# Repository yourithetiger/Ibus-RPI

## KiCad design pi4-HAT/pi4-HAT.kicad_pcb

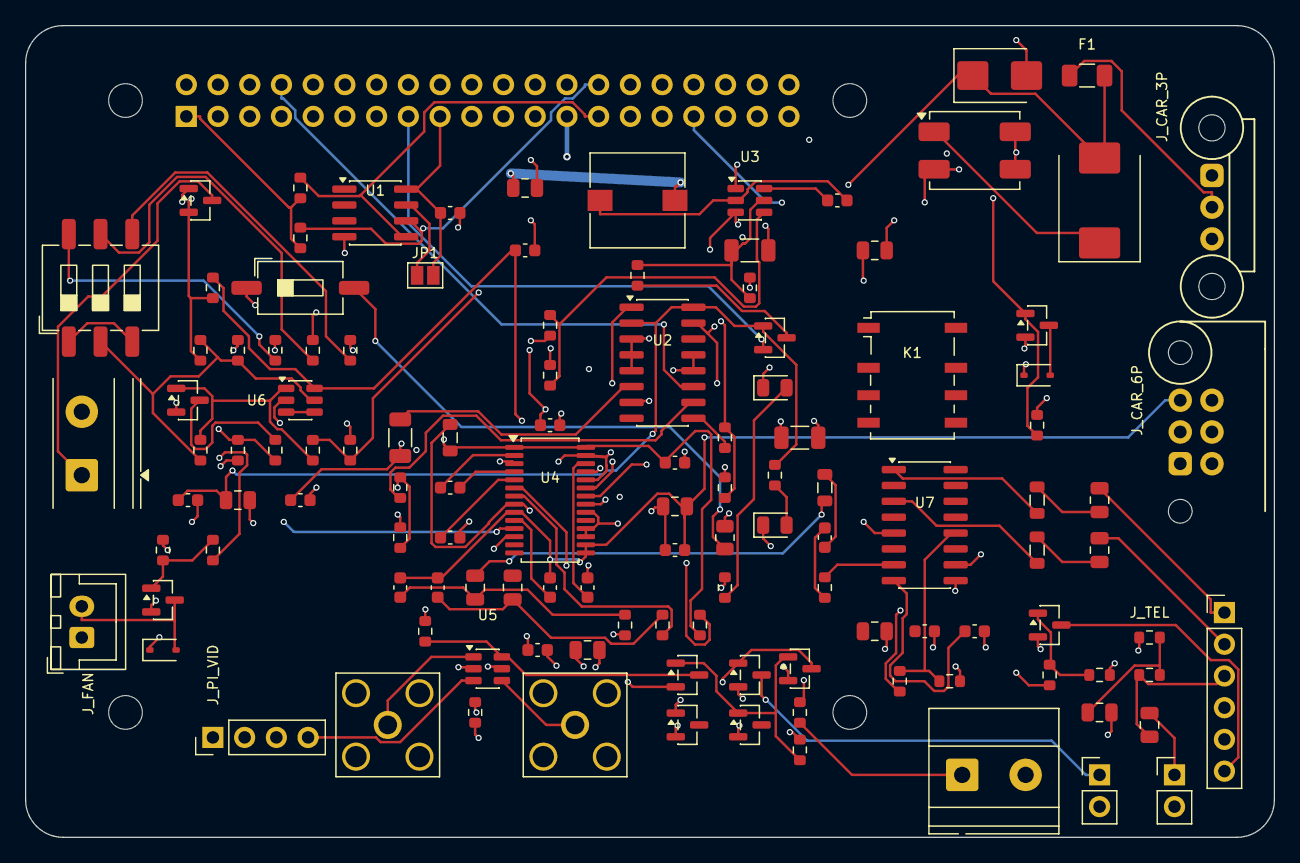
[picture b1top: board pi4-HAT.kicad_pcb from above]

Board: 4 copper layers, 100.0 x 65.0 mm, 125 parts (1 on the bottom side), 91 nets.

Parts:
C1: 100n; C_0603_1608Metric
C2: 10uF_50V; C_1206_3216Metric
C3, C5, C11, C14, C16, C22, C23, C25: 100nF; C_0603_1608Metric
C4: 47uF; C_1206_3216Metric
C6, C7: 22uF; C_0805_2012Metric
C9: 220pF; C_0603_1608Metric
C10, C15, C19, C20, C24, C26, C30, C31, C32, C33: 10uF; C_0805_2012Metric
C12, C13: 2.2uF; C_0603_1608Metric
C17, C18: 2.2nF; C_0603_1608Metric
C21: 10uF; C_0603_1608Metric
C27: 0.1uF; C_0603_1608Metric
C28, C29: 1uF; C_0603_1608Metric
D1: SMBJ18A; D_SMB
D2: SS34; D_SMC
D3, D9, D11: BAT54C; SOT-23
D4: GREEN; LED_0805_2012Metric
D5: BLUE; LED_0805_2012Metric
D7, D10: 1N4148; D_SOD-323
D8: BZX84C3V3; SOT-23
D12: BZX84C4V7; SOT-23
F1: 5A; Fuse_1206_3216Metric
FB1, FB2, FB3: 120R/2A; L_0805_2012Metric
FL1: ACM70V-701-2PL; L_CommonModeChoke_TDK_ACM7060
J1: GPIO; PinSocket_2x20_P2.54mm_Vertical
JP1: ID_WP; SolderJumper-2_P1.3mm_Open_Pad1.0x1.5mm
J_CAR_3P: TE_953442-1; TE_MQS_3PIN
J_CAR_6P: TE_966871-1; TE_MQS_6PIN
J_DVR: TE_MKDS_2P; TerminalBlock_Phoenix_MKDS-1,5-2-5.08_1x02_P5.08mm_Horizont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
J_FAN: JST_2P_FAN; JST_XH_B2B-XH-A_1x02_P2.50mm_Vertical
J_MIC: MIC_OUT_USB; PinHeader_1x02_P2.54mm_Vertical
J_PI_VID: TRRS_3.5mm_PI; PinHeader_1x04_P2.54mm_Vertical
J_RCA_CAM: RCA_CAM_IN; SMA_Amphenol_132203-12_Horizontal
J_RCA_TV: RCA_TV_OUT; SMA_Amphenol_132203-12_Horizontal
J_REV: MKDS_REV_12V; TerminalBlock_Phoenix_MKDS-1,5-2-5.08_1x02_P5.08mm_Horizont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
J_TEL: TCU_IO_DB25; PinHeader_1x06_P2.54mm_Vertical
J_TV_TRIG: TV_PIN17_TRIG; PinHeader_1x02_P2.54mm_Vertical
K1: G6K-2F-Y-5VDC; Relay_DPDT_Omron_G6K-2F-Y
L1: 10uH; L_Wuerth_WE-PD-Typ-7345
L2: BLM21PG221SN1D; L_0805_2012Metric
MH1, MH2, MH3, MH4: MountingHole_2.7mm_M2.5
Q1, Q2, Q3, Q5, Q6: 2N7002; SOT-23
Q4: DMP32D4S; SOT-23
R1, R2: 3.9k; R_0603_1608Metric
R3: 100k_1%; R_0603_1608Metric
R4: 13.3k_1%; R_0603_1608Metric
R5, R8, R10, R13, R14, R39, R41: 1k; R_0603_1608Metric
R6: 1M; R_0603_1608Metric
R7: 10_1W; R_1206_3216Metric
R9, R11: 2k; R_0603_1608Metric
R12: 10k; R_0805_2012Metric
R16, R24, R25, R26, R35, R36, R40, R42: 100k; R_0603_1608Metric
R17, R18: 470; R_0603_1608Metric
R19, R22, R37, R43: 10k; R_0603_1608Metric
R23: 3.3k; R_0603_1608Metric
R27, R44: 100; R_0603_1608Metric
R28: 680k; R_0603_1608Metric
R29: 1.00M_1%; R_0603_1608Metric
R30: 1.00M; R_0603_1608Metric
R31: 118k_1%; R_0603_1608Metric
R32: 115k_1%; R_0603_1608Metric
R33: 113k_1%; R_0603_1608Metric
R34: 10M; R_0603_1608Metric
R38: 20k; R_0603_1608Metric
R45: 2.2k; R_0603_1608Metric
SW_BENCH: SW_BENCH; SW_DIP_SPSTx01_Slide_6.7x4.1mm_W8.61mm_P2.54mm_LowProfile
SW_DVR_CFG: DIP-3; SW_DIP_SPSTx03_Slide_6.7x9.18mm_W8.61mm_P2.54mm_LowProfile
U1: CAT24C256; SOIC-8_3.9x4.9mm_P1.27mm
U2: TH3122.4; SOIC-16_3.9x9.9mm_P1.27mm
U3: TPS54302; SOT-23-6
U4: PCM5122PW; TSSOP-28_4.4x9.7mm_P0.65mm
U5: TS5A3159; SOT-23-6
U6: TLV3012; SOT-23-6
U7: PAM8406D; SOIC-16_3.9x9.9mm_P1.27mm

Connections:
+3V3: C1.1, C14.1, J1.1, J1.17, JP1.2, L2.1, R1.1, R2.1, R19.1, U1.8, U4.1, U4.28
+5V: C6.1, C7.1, C23.1, C24.1, D7.1, D10.1, J1.2, J1.4, J_FAN.1, L1.2, R3.1, R13.2, R44.1, U5.5, U7.5, U7.9
+12V_IN: C2.1, C3.1, FL1.2, SW_BENCH.1, U2.1, U2.15, U3.3
AGND: C15.2, C16.2, C17.2, C18.2, C21.2, J_CAR_6P.3, J_CAR_6P.6, U4.9, U4.15, U4.16
AVDD_3V3: C15.1, C16.1, L2.2, U4.8
BENCH_PULLUP: R12.1, SW_BENCH.2
BOOT_NODE: C5.1, U3.6
BUCK_EN: C4.1, R5.2, R6.1, U3.5
BUCK_FB: R3.2, R4.1, U3.4
CAM_TRIG_GND: J_TV_TRIG.1, Q2.3
CAM_VID: J_RCA_CAM.1, U5.1
DAC_CAPM: C12.2, U4.4
DAC_CAPP: C12.1, U4.2
DAC_FLT_L: C17.1, C19.1, R17.2
DAC_FLT_R: C18.1, C20.1, R18.2
DAC_LDOO: C22.1, U4.26
DAC_OUTL_RAW: R17.1, U4.6
DAC_OUTR_RAW: R18.1, U4.7
DAC_VCOM: C21.1, U4.10
DAC_VNEG: C13.1, U4.5
DAC_XSMT: R19.2, U4.25
DVR_12V_OUT: J_DVR.1, Q4.3
DVR_COMP_OUT: Q3.1, R34.2, R37.1, U6.1
DVR_GATE_PULL: Q3.3, R36.2
DVR_PMOS_GATE: Q4.1, R35.2, R36.1
DVR_SENSE: R29.2, R30.1, R34.1, SW_DVR_CFG.2, U6.5
DVR_VCC_5V: C25.1, D12.1, R28.2, U6.6
FAN_GATE: Q5.1, R26.1, R27.2
FAN_NEG: D10.2, J_FAN.2, Q5.3
GND: C1.2, C2.2, C3.2, C4.2, C6.2, C7.2, C9.2, C10.2, C11.2, C13.2, C14.2, C22.2, C23.2, C24.2, C25.2, C26.2, C27.2, C28.2, C32.2, D1.2, D4.1, D5.1, D8.2, D12.2, FL1.3, FL1.4, J1.6, J1.9, J1.14, J1.20, J1.25, J1.30, J1.34, J1.39, J_CAR_3P.1, J_DVR.2, J_MIC.2, J_PI_VID.3, J_RCA_CAM.2, J_RCA_TV.2, J_REV.2, J_TEL.4, J_TV_TRIG.2, Q1.2, Q2.2, Q3.2, Q5.2, Q6.2, R4.2, R6.2, R9.2, R11.2, R16.2, R23.2, R24.2, R25.2, R26.2, R30.2, R31.2, R32.2, R33.2, R38.2, R40.2, R42.2, U1.4, U2.3, U2.4, U2.5, U2.7, U2.12, U2.13, U3.1, U4.3, U4.17, U4.18, U4.20, U4.24, U4.27, U5.2, U6.2, U7.10
GPIO2/SDA1: J1.3, U4.11
GPIO3/SCL1: J1.5, U4.12
GPIO12/PWM0: J1.32, R27.1
GPIO13/PWM1: J1.33, R22.2
GPIO14/TXD0: J1.8, U2.11
GPIO15/RXD0: J1.10, R8.2, R9.1
GPIO16: J1.36, R10.2, R11.1
GPIO17: J1.11, R41.1
GPIO18/PCM.CLK: J1.12, U4.21
GPIO19/PCM.FS: J1.35, U4.23
GPIO21/PCM.DOUT: J1.40, U4.22
GPIO22: D3.2, J1.15
GPIO23: J1.16, R39.1
GPIO24: D11.2, J1.18
GPIO25: D9.2, J1.22
GPIO26: J1.37, R37.2, R38.1
IBUS: C9.1, J_CAR_3P.3, R7.1, R12.2
IBUS_5V: C10.1, C11.1, D3.1, R14.2, U2.2, U2.16
ID_SCL: J1.28, R2.2, U1.6
ID_SDA: J1.27, R1.2, U1.5
KL30: F1.1, J_CAR_3P.2
LED_5V_ANODE: D4.2, R13.1
LED_IBUS_ANODE: D5.2, R14.1
unnamed: C28.1, U7.8
unnamed: C29.1, FB3.2
unnamed: C29.2, R43.1
unnamed: C30.1, FB1.2
unnamed: C30.2, J_TEL.1
unnamed: C31.1, FB2.2
unnamed: C31.2, J_TEL.2
unnamed: C32.1, R44.2, R45.2
unnamed: C33.1, J_TEL.3, R45.1
unnamed: C33.2, J_MIC.1
unnamed: FB1.1, U7.1
unnamed: FB2.1, U7.3
unnamed: JP1.1, U1.7
unnamed: J_TEL.6, Q6.3
unnamed: Q6.1, R39.2, R40.1
unnamed: R31.1, SW_DVR_CFG.6
unnamed: R32.1, SW_DVR_CFG.5
unnamed: R33.1, SW_DVR_CFG.4
unnamed: R41.2, R42.1, U7.12
unnamed: R43.2, U7.7
unnamed: SW_DVR_CFG.1, SW_DVR_CFG.3
unnamed: U6.3, U6.4
PI_AUDIO_L: C19.2, FB3.1
PI_VID: J_PI_VID.4, U5.3
PWR_KEEP_ALIVE: D3.3, R5.1
RELAY_COIL_NEG: D7.2, Q1.3
RELAY_CTRL: J1.13, Q1.1, R16.1
REV_12V_IN: J_REV.1, R22.1
REV_SENSE_3V3: D8.1, D9.1, D11.1, R23.1
SW_NODE: C5.2, L1.1, U3.2
TH3122_IBUS: R7.2, U2.6
TH3122_RXD: R8.1, U2.10
TH3122_SEN_STA: R10.1, U2.9
TV_TRIG_GATE: D9.3, Q2.1, R25.1
TV_VID_OUT: J_RCA_TV.1, U5.4
VFILT: D2.1, FL1.1
VID_SEL: D11.3, R24.1, U5.6
VRAW: D1.1, D2.2, F1.2, Q4.2, R28.1, R29.1, R35.1

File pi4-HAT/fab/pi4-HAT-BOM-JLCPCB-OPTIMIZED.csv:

Comment,Designator,Footprint,LCSC Part #
100nF,"C1,C3,C5,C11,C14,C16,C22,C23,C25,C27",C_0603_1608Metric,C14663
10uF,C2,C_1206_3216Metric,C13585
47uF,C4,C_1206_3216Metric,C96937
22uF,"C6,C7",C_0805_2012Metric,C45783
220pF,C9,C_0603_1608Metric,C1600
10uF,"C10,C15,C19,C20,C24,C26,C30,C31,C32,C33",C_0805_2012Metric,C15850
2.2uF,"C12,C13",C_0603_1608Metric,C23630
2.2nF,"C17,C18",C_0603_1608Metric,C1591
10uF,C21,C_0603_1608Metric,C19702
1uF,"C28,C29",C_0603_1608Metric,C15849
BAT54C,"D3,D9,D11",SOT-23,C8596
GREEN,D4,LED_0805_2012Metric,C2297
BLUE,D5,LED_0805_2012Metric,C2293
1N4148,"D7,D10",D_SOD-323,C81598
BZX84C3V3,D8,SOT-23,C8675
120R/2A,"FB1,FB2,FB3",L_0805_2012Metric,C1015
BLM21PG221SN1D,L2,L_0805_2012Metric,C1035
2N7002,"Q1,Q2,Q3,Q5,Q6",SOT-23,C8598
DMP32D4S,Q4,SOT-23,C151273
3.9k,"R1,R2",R_0603_1608Metric,C22985
100k,"R3,R16,R24,R25,R26,R35,R36,R40,R42",R_0603_1608Metric,C25803
1k,"R5,R8,R10,R13,R14,R39,R41",R_0603_1608Metric,C21190
1M,"R6,R29,R30",R_0603_1608Metric,C22935
10,R7,R_1206_3216Metric,C17935
2k,"R9,R11",R_0603_1608Metric,C21198
10k,R12,R_0805_2012Metric,C17414
470,"R17,R18",R_0603_1608Metric,C23179
10k,"R19,R22,R37,R43",R_0603_1608Metric,C25804
3.3k,R23,R_0603_1608Metric,C22978
100,"R27,R44",R_0603_1608Metric,C22775
680k,R28,R_0603_1608Metric,C23206
10M,R34,R_0603_1608Metric,C125141
20k,R38,R_0603_1608Metric,C25760
2.2k,R45,R_0603_1608Metric,C21199
CAT24C256,U1,SOIC-8_3.9x4.9mm_P1.27mm,C146734
TPS54302,U3,SOT-23-6,C311983
PCM5122PW,U4,TSSOP-28_4.4x9.7mm_P0.65mm,C962071
TS5A3159,U5,SOT-23-6,C92485
PAM8406D,U7,SOIC-16_3.9x9.9mm_P1.27mm,C86270

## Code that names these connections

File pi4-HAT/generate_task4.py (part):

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import uuid
import shutil

SCHEMATIC_PATH = "/home/Youri621/E39Project/Ibus-RPI/pi4-HAT/pi4-HAT.kicad_sch"
BACKUP_PATH = "/home/Youri621/E39Project/Ibus-RPI/pi4-HAT/pi4-HAT.kicad_sch.bak_task3"

# Restore clean backup from task 3
shutil.copy(BACKUP_PATH, SCHEMATIC_PATH)
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# BLOCK A: Autonomous Low-Voltage Cutoff for DVR (X: 320..415, Y: 85..155)
# =========================================================================
# R28 (680k) rot=90: local pins (0, 2.54), (0, -2.54)
# pin 1: transform(325.12, 91.44, 0, 2.54, 90) = (322.58, 91.44) -> VRAW
# pin 2: transform(325.12, 91.44, 0, -2.54, 90) = (327.66, 91.44) -> DVR_VCC_5V
add_inst("Device:R_Small", "R28", "680k", "Resistor_SMD:R_0603_1608Metric", 325.12, 91.44, rot=90, pin_count=2)
p1 = transform(325.12, 91.44, 0, 2.54, 90)
p2 = transform(325.12, 91.44, 0, -2.54, 90)
add_label("VRAW", p1[0], p1[1], rot=180)
add_label("DVR_VCC_5V", p2[0], p2[1], rot=0)

# D12 (BZX84C4V7 Zener) rot=90: local pins K: (-2.54, 0), A: (2.54, 0)
# K: transform(335.28, 91.44, -2.54, 0, 90) = (335.28, 93.98) -> DVR_VCC_5V
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add_inst("Device:D_Zener_Small", "D12", "BZX84C4V7", "Package_TO_SOT_SMD:SOT-23", 335.28, 91.44, rot=90, pin_count=2)
pk = transform(335.28, 91.44, -2.54, 0, 90)
pa = transform(335.28, 91.44, 2.54, 0, 90)
add_label("DVR_VCC_5V", pk[0], pk[1], rot=270)
add_label("GND", pa[0], pa[1], rot=90)

# C25 (100nF) rot=0: local pins (0, 2.54), (0, -2.54)
# pin 1: (345.44, 91.44 - 2.54) = (345.44, 88.9) -> DVR_VCC_5V
# pin 2: (345.44, 91.44 + 2.54) = (345.44, 93.98) -> GND
add_inst("Device:C_Small", "C25", "100nF", "Capacitor_SMD:C_0603_1608Metric", 345.44, 91.44, rot=0, pin_count=2)
p1 = transform(345.44, 91.44, 0, 2.54, 0)
p2 = transform(345.44, 91.44, 0, -2.54, 0)
add_label("DVR_VCC_5V", p1[0], p1[1], rot=90)
add_label("GND", p2[0], p2[1], rot=270)
# Add PWR_FLAG on DVR_VCC_5V
add_pwr_flag(p1[0], p1[1])
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p_inp = transform(355.6, 121.92, -10.16, 3.81, 0)
p_vcc = transform(355.6, 121.92, 0, 8.89, 0)

add_label("DVR_COMP_OUT", p_out[0], p_out[1], rot=0)
add_label("GND", p_gnd[0], p_gnd[1], rot=270)
add_label("DVR_SENSE", p_inp[0], p_inp[1], rot=180)
add_label("DVR_VCC_5V", p_vcc[0], p_vcc[1], rot=90)
# Connect Pin 3 (REF) to Pin 4 (IN-)
add_wire(p_ref[0], p_ref[1], p_ref[0] - 2.54, p_ref[1])
add_wire(p_ref[0] - 2.54, p_ref[1], p_inm[0] - 2.54, p_inm[1])
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add_inst("Device:R_Small", "R29", "1.00M_1%", "Resistor_SMD:R_0603_1608Metric", 325.12, 114.3, rot=90, pin_count=2)
p1 = transform(325.12, 114.3, 0, 2.54, 90)
p2 = transform(325.12, 114.3, 0, -2.54, 90)
add_label("VRAW", p1[0], p1[1], rot=180)
add_label("DVR_SENSE", p2[0], p2[1], rot=0)

add_inst("Device:R_Small", "R30", "1.00M", "Resistor_SMD:R_0603_1608Metric", 325.12, 127.0, rot=90, pin_count=2)
p1 = transform(325.12, 127.0, 0, 2.54, 90)
p2 = transform(325.12, 127.0, 0, -2.54, 90)
add_label("DVR_SENSE", p1[0], p1[1], rot=180)
add_label("GND", p2[0], p2[1], rot=0)

add_inst("Device:R_Small", "R34", "10M", "Resistor_SMD:R_0603_1608Metric", 355.6, 142.24, rot=90, pin_count=2)
p1 = transform(355.6, 142.24, 0, 2.54, 90)
p2 = transform(355.6, 142.24, 0, -2.54, 90)
add_label("DVR_SENSE", p1[0], p1[1], rot=180)
add_label("DVR_COMP_OUT", p2[0], p2[1], rot=0)

# DIP Switch SW_DVR_CFG at (325.12, 149.86) rot=0
# Left pins:
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p_sw2 = transform(325.12, 149.86, -7.62, 0, 0)
p_sw3 = transform(325.12, 149.86, -7.62, -2.54, 0)
add_wire(p_sw1[0], p_sw1[1], p_sw3[0], p_sw3[1])
add_label("DVR_SENSE", p_sw2[0], p_sw2[1], rot=180)

p_sw6 = transform(325.12, 149.86, 7.62, 2.54, 0)
p_sw5 = transform(325.12, 149.86, 7.62, 0, 0)
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q3_g = transform(381.0, 121.92, -5.08, 0, 0)
q3_s = transform(381.0, 121.92, 2.54, -5.08, 0)
q3_d = transform(381.0, 121.92, 2.54, 5.08, 0)
add_label("DVR_COMP_OUT", q3_g[0], q3_g[1], rot=180)
add_label("GND", q3_s[0], q3_s[1], rot=270)
add_label("DVR_GATE_PULL", q3_d[0], q3_d[1], rot=90)

# R35 (100k) & R36 (100k)
add_inst("Device:R_Small", "R35", "100k", "Resistor_SMD:R_0603_1608Metric", 393.7, 104.14, rot=90, pin_count=2)
p1 = transform(393.7, 104.14, 0, 2.54, 90)
p2 = transform(393.7, 104.14, 0, -2.54, 90)
add_label("VRAW", p1[0], p1[1], rot=180)
add_label("DVR_PMOS_GATE", p2[0], p2[1], rot=0)

add_inst("Device:R_Small", "R36", "100k", "Resistor_SMD:R_0603_1608Metric", 393.7, 116.84, rot=90, pin_count=2)
p1 = transform(393.7, 116.84, 0, 2.54, 90)
p2 = transform(393.7, 116.84, 0, -2.54, 90)
add_label("DVR_PMOS_GATE", p1[0], p1[1], rot=180)
add_label("DVR_GATE_PULL", p2[0], p2[1], rot=0)

# P-MOSFET Q4 (DMP32D4S) at (406.4, 104.14) rot=0
# G: local (-5.08, 0)    -> (401.32, 104.14)
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q4_g = transform(406.4, 104.14, -5.08, 0, 0)
q4_s = transform(406.4, 104.14, 2.54, -5.08, 0)
q4_d = transform(406.4, 104.14, 2.54, 5.08, 0)
add_label("DVR_PMOS_GATE", q4_g[0], q4_g[1], rot=180)
add_label("VRAW", q4_s[0], q4_s[1], rot=270)
add_label("DVR_12V_OUT", q4_d[0], q4_d[1], rot=90)

# Screw terminal J_DVR (Conn_01x02) at (419.1, 99.06) rot=0
# Pin 1: local (-5.08, 0)     -> (414.02, 99.06) -> DVR_12V_OUT
# Pin 2: local (-5.08, -2.54) -> (414.02, 101.6) -> GND
add_inst("Connector_Generic:Conn_01x02", "J_DVR", "TE_MKDS_2P", "TerminalBlock_Phoenix:TerminalBlock_Phoenix_MKDS-1,5-2-5.08_1x02_P5.08mm_Horizontal", 419.1, 99.06, rot=0, pin_count=2)
jd_p1 = transform(419.1, 99.06, -5.08, 0, 0)
jd_p2 = transform(419.1, 99.06, -5.08, -2.54, 0)
add_label("DVR_12V_OUT", jd_p1[0], jd_p1[1], rot=180)
add_label("GND", jd_p2[0], jd_p2[1], rot=180)

# Pi Monitoring Divider R37 (10k), R38 (20k) -> GPIO26
add_inst("Device:R_Small", "R37", "10k", "Resistor_SMD:R_0603_1608Metric", 375.92, 137.16, rot=90, pin_count=2)
p1 = transform(375.92, 137.16, 0, 2.54, 90)
p2 = transform(375.92, 137.16, 0, -2.54, 90)
add_label("DVR_COMP_OUT", p1[0], p1[1], rot=180)
add_label("GPIO26", p2[0], p2[1], rot=0)

add_inst("Device:R_Small", "R38", "20k", "Resistor_SMD:R_0603_1608Metric", 391.16, 137.16, rot=90, pin_count=2)
p1 = transform(391.16, 137.16, 0, 2.54, 90)
p2 = transform(391.16, 137.16, 0, -2.54, 90)
add_label("GPIO26", p1[0], p1[1], rot=180)
add_label("GND", p2[0], p2[1], rot=0)


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add_inst("Connector_Generic:Conn_01x02", "J_REV", "MKDS_REV_12V", "TerminalBlock_Phoenix:TerminalBlock_Phoenix_MKDS-1,5-2-5.08_1x02_P5.08mm_Horizontal", 129.54, 256.54, rot=0, pin_count=2)
p1 = transform(129.54, 256.54, -5.08, 0, 0)
p2 = transform(129.54, 256.54, -5.08, -2.54, 0)
add_label("REV_12V_IN", p1[0], p1[1], rot=180)
add_label("GND", p2[0], p2[1], rot=180)

# Divider R22 (10k), R23 (3.3k) & D8 (3.3V Zener) -> GPIO13{slash}PWM1
add_inst("Device:R_Small", "R22", "10k", "Resistor_SMD:R_0603_1608Metric", 142.24, 256.54, rot=90, pin_count=2)
p1 = transform(142.24, 256.54, 0, 2.54, 90)
p2 = transform(142.24, 256.54, 0, -2.54, 90)
add_label("REV_12V_IN", p1[0], p1[1], rot=180)
add_label("REV_SENSE_3V3", p2[0], p2[1], rot=0)
add_label("GPIO13{slash}PWM1", p2[0], p2[1], rot=0)

add_inst("Device:R_Small", "R23", "3.3k", "Resistor_SMD:R_0603_1608Metric", 154.94, 256.54, rot=0, pin_count=2)
# rot=0 -> p1 (0, 2.54) -> (154.94, 254.0), p2 (0, -2.54) -> (154.94, 259.08)
p1 = transform(154.94, 256.54, 0, 2.54, 0)
p2 = transform(154.94, 256.54, 0, -2.54, 0)
add_label("REV_SENSE_3V3", p1[0], p1[1], rot=90)
add_label("GND", p2[0], p2[1], rot=270)

add_inst("Device:D_Zener_Small", "D8", "BZX84C3V3", "Package_TO_SOT_SMD:SOT-23", 165.1, 256.54, rot=90, pin_count=2)
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# So pk is at 259.08 and pa is at 254.0!
pk = transform(165.1, 256.54, -2.54, 0, 90)
pa = transform(165.1, 256.54, 2.54, 0, 90)
add_label("REV_SENSE_3V3", pk[0], pk[1], rot=270)
add_label("GND", pa[0], pa[1], rot=90)

# Diode-OR D9 (BAT54C) for TV Pin 17 ground trigger
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p1 = transform(177.8, 256.54, -7.62, 0, 0)
p2 = transform(177.8, 256.54, 7.62, 0, 0)
p3 = transform(177.8, 256.54, 0, -5.08, 0)
add_label("REV_SENSE_3V3", p1[0], p1[1], rot=180)
add_label("GPIO25", p2[0], p2[1], rot=0)
add_label("TV_TRIG_GATE", p3[0], p3[1], rot=270)

# Pull-down R25 (100k) rot=0
add_inst("Device:R_Small", "R25", "100k", "Resistor_SMD:R_0603_1608Metric", 177.8, 269.24, rot=0, pin_count=2)
p1 = transform(177.8, 269.24, 0, 2.54, 0)
p2 = transform(177.8, 269.24, 0, -2.54, 0)
add_label("TV_TRIG_GATE", p1[0], p1[1], rot=90)
add_label("GND", p2[0], p2[1], rot=270)

# Transistor Q2 (2N7002) at (195.58, 256.54) rot=0
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q2_g = transform(195.58, 256.54, -5.08, 0, 0)
q2_s = transform(195.58, 256.54, 2.54, -5.08, 0)
q2_d = transform(195.58, 256.54, 2.54, 5.08, 0)
add_label("TV_TRIG_GATE", q2_g[0], q2_g[1], rot=180)
add_label("GND", q2_s[0], q2_s[1], rot=270)
add_label("CAM_TRIG_GND", q2_d[0], q2_d[1], rot=90)

# J_TV_TRIG (Conn_01x02) at (208.28, 251.46) rot=0
# Pin 1: (-5.08, 0)     -> (203.2, 251.46) -> CAM_TRIG_GND
# Pin 2: (-5.08, -2.54) -> (203.2, 254.0)  -> GND
add_inst("Connector_Generic:Conn_01x02", "J_TV_TRIG", "TV_PIN17_TRIG", "Connector_PinHeader_2.54mm:PinHeader_1x02_P2.54mm_Vertical", 208.28, 251.46, rot=0, pin_count=2)
p1 = transform(208.28, 251.46, -5.08, 0, 0)
p2 = transform(208.28, 251.46, -5.08, -2.54, 0)
add_label("CAM_TRIG_GND", p1[0], p1[1], rot=180)
add_label("GND", p2[0], p2[1], rot=180)
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
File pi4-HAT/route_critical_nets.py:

import pcbnew

BOARD_PATH = "/home/Youri621/E39Project/Ibus-RPI/pi4-HAT/pi4-HAT.kicad_pcb"
board = pcbnew.LoadBoard(BOARD_PATH)

def mm(v):
    return pcbnew.FromMM(v)

def add_track(board, net_name, layer, width_mm, pts):
    net = board.FindNet(net_name)
    if not net:
        print(f"Warning: Net {net_name} not found!")
        return
    for i in range(len(pts) - 1):
        x1, y1 = pts[i]
        x2, y2 = pts[i + 1]
        t = pcbnew.PCB_TRACK(board)
        t.SetStart(pcbnew.VECTOR2I(mm(x1), mm(y1)))
        t.SetEnd(pcbnew.VECTOR2I(mm(x2), mm(y2)))
        t.SetWidth(mm(width_mm))
        t.SetLayer(layer)
        t.SetNet(net)
        board.Add(t)

def add_via(board, net_name, x, y, size_mm=0.8, drill_mm=0.4):
    net = board.FindNet(net_name)
    if not net:
        return
    v = pcbnew.PCB_VIA(board)
    v.SetPosition(pcbnew.VECTOR2I(mm(x), mm(y)))
    v.SetWidth(mm(size_mm))
    v.SetDrill(mm(drill_mm))
    v.SetViaType(pcbnew.VIATYPE_THROUGH)
    v.SetNet(net)
    board.Add(v)

# -------------------------------------------------------------
# 1. BUCK CONVERTER POWER LOOP (12V -> 5V 3.5A)
# -------------------------------------------------------------
# KL30: J_CAR_3P Pin 2 to F1 Pin 1
add_track(board, "KL30", pcbnew.F_Cu, 1.5, [
    (195.0, 64.54), (189.0, 64.54), (189.0, 57.4), (186.0, 57.4)
])

# VRAW: F1 Pin 2 to D1 Pin 1 and FL1 Pin 1
add_track(board, "VRAW", pcbnew.F_Cu, 1.5, [
    (186.0, 54.6), (186.0, 60.0), (183.85, 64.0)
])
add_track(board, "VRAW", pcbnew.F_Cu, 1.5, [
    (183.85, 64.0), (180.0, 64.0), (180.0, 58.5), (172.75, 58.5)
])
# D2 TVS to VRAW
add_track(board, "VRAW", pcbnew.F_Cu, 1.5, [
    (172.75, 58.5), (172.75, 66.0), (179.4, 68.0)
])

# VFILT: FL1 Pin 2 to C6 Pin 1 and U3 Pin 2 (VIN)
add_track(board, "VFILT", pcbnew.F_Cu, 1.5, [
    (172.75, 61.5), (165.0, 61.5), (161.05, 64.0), (156.86, 64.0)
])

# SW_NODE: U3 Pin 6 to L1 Pin 1 and C5 Pin 1
add_track(board, "SW_NODE", pcbnew.F_Cu, 1.5, [
    (159.14, 63.05), (154.0, 63.05), (146.0, 64.0)
])
add_track(board, "SW_NODE", pcbnew.F_Cu, 0.6, [
    (159.14, 63.05), (163.0, 63.05), (165.0, 64.0)
])

# +5V: L1 Pin 2 to C7 Pin 1 and to Pi 4 GPIO J1 Pins 2 & 4
add_track(board, "+5V", pcbnew.F_Cu, 1.8, [
    (152.0, 64.0), (145.0, 64.0), (139.05, 63.0), (125.0, 63.0), (118.0, 59.0), (115.41, 54.73)
])
add_track(board, "+5V", pcbnew.F_Cu, 1.8, [
    (115.41, 54.73), (112.87, 54.73)
])
# Power vias down to In2.Cu power plane
add_via(board, "+5V", 143.0, 63.0, size_mm=1.0, drill_mm=0.5)
add_via(board, "+5V", 125.0, 63.0, size_mm=1.0, drill_mm=0.5)

# -------------------------------------------------------------
# 2. CONTROLLED 75-OHM VIDEO LINES
# -------------------------------------------------------------
# PI_VID: J_PI_VID Pin 4 to U5 Pin 3
add_track(board, "PI_VID", pcbnew.F_Cu, 0.25, [
    (122.62, 107.0), (128.0, 107.0), (132.0, 102.45), (135.86, 102.45)
])

# CAM_VID: J_RCA_CAM Pin 1 to U5 Pin 1
add_track(board, "CAM_VID", pcbnew.F_Cu, 0.25, [
    (129.0, 106.0), (131.0, 104.0), (131.0, 100.55), (135.86, 100.55)
])

# TV_VID_OUT: U5 Pin 4 to J_RCA_TV Pin 1
add_track(board, "TV_VID_OUT", pcbnew.F_Cu, 0.25, [
    (138.14, 102.45), (141.0, 102.45), (144.0, 106.0)
])

# -------------------------------------------------------------
# 3. I2S DIGITAL AUDIO BUS (routed on B.Cu)
# -------------------------------------------------------------
# GPIO18/PCM.CLK -> U4 Pin 23
add_track(board, "GPIO18{slash}PCM.CLK", pcbnew.B_Cu, 0.25, [
    (125.57, 54.73), (125.57, 75.0), (141.0, 83.0), (144.86, 87.03)
])

# GPIO19/PCM.FS -> U4 Pin 24
add_track(board, "GPIO19{slash}PCM.FS", pcbnew.B_Cu, 0.25, [
    (156.05, 57.27), (156.05, 75.0), (148.0, 83.0), (144.86, 86.38)
])

# GPIO21/PCM.DOUT -> U4 Pin 22
add_track(board, "GPIO21{slash}PCM.DOUT", pcbnew.B_Cu, 0.25, [
    (161.13, 54.73), (161.13, 77.0), (150.0, 85.0), (144.86, 87.68)
])

# I2C Control to DAC: SDA & SCL
add_track(board, "GPIO2{slash}SDA1", pcbnew.B_Cu, 0.25, [
    (115.41, 57.27), (115.41, 70.0), (132.0, 85.0), (139.14, 90.28)
])
add_track(board, "GPIO3{slash}SCL1", pcbnew.B_Cu, 0.25, [
    (117.95, 57.27), (117.95, 71.0), (133.0, 86.0), (139.14, 90.93)
])

# -------------------------------------------------------------
# 4. TELEPHONY DIFFERENTIAL AUDIO & CONTROLS
# -------------------------------------------------------------
# U7 Pin 1 (+OUT_L) -> FB1 -> C30 -> J_TEL Pin 1 (TEL_OUT+)
add_track(board, "Net-(FB1-Pad1)", pcbnew.F_Cu, 0.4, [
    (169.53, 85.56), (175.0, 85.56), (181.0, 86.94)
])
add_track(board, "Net-(C30-Pad1)", pcbnew.F_Cu, 0.4, [
    (181.0, 89.06), (186.0, 88.95)
])
add_track(board, "Net-(C30-Pad2)", pcbnew.F_Cu, 0.4, [
    (186.0, 87.05), (191.0, 87.05), (196.0, 97.0)
])

# U7 Pin 3 (-OUT_L) -> FB2 -> C31 -> J_TEL Pin 2 (TEL_OUT-)
add_track(board, "Net-(FB2-Pad1)", pcbnew.F_Cu, 0.4, [
    (169.53, 88.10), (175.0, 88.10), (181.0, 90.94)
])
add_track(board, "Net-(C31-Pad1)", pcbnew.F_Cu, 0.4, [
    (181.0, 93.06), (186.0, 92.95)
])
add_track(board, "Net-(C31-Pad2)", pcbnew.F_Cu, 0.4, [
    (186.0, 91.05), (191.0, 91.05), (196.0, 99.54)
])

# TEL_MUTE: Q6 Pin 3 (Drain) to J_TEL Pin 6
add_track(board, "TEL_MUTE", pcbnew.F_Cu, 0.35, [
    (182.94, 98.0), (189.0, 98.0), (196.0, 109.7)
])

# -------------------------------------------------------------
# 5. I-BUS UART BUS (TH3122.4 Transceiver)
# -------------------------------------------------------------
# J_CAR_3P Pin 3 (IBUS) to U2 Pin 16
add_track(board, "IBUS", pcbnew.B_Cu, 0.4, [
    (195.0, 67.08), (175.0, 67.08), (160.0, 72.56), (153.48, 72.56)
])

# U2 Pin 12 (TXD) -> J1 Pin 8 (TXD0)
add_track(board, "GPIO14{slash}TXD0", pcbnew.B_Cu, 0.25, [
    (153.48, 77.64), (135.0, 77.64), (120.49, 65.0), (120.49, 54.73)
])

# U2 Pin 10 (RXD) -> J1 Pin 10 (RXD0)
add_track(board, "GPIO15{slash}RXD0", pcbnew.B_Cu, 0.25, [
    (153.48, 80.18), (137.0, 80.18), (123.03, 66.0), (123.03, 54.73)
])

# U2 Pin 9 (SEN/STA) -> J1 Pin 7 (GPIO4)
add_track(board, "TH3122_SEN_STA", pcbnew.B_Cu, 0.25, [
    (153.48, 81.45), (138.0, 81.45), (120.49, 68.0), (120.49, 57.27)
])

board.Save(BOARD_PATH)
print("All 5 critical buses successfully routed.")

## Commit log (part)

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2026-05-24 Basic readme
2026-05-24 readme
2026-05-24 readme cleanup
2026-05-24 arduino control for audio relay
2026-05-24 ibus service v1 before going in car
2026-05-24 change for resler auto detect
2026-05-24 systemd service
2026-05-24 fix strange logs
2026-05-24 some fixes
2026-05-24 new cdc code
2026-05-24 fix try
2026-05-24 fix lines
2026-05-24 fix echange
